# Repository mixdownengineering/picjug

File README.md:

PICJUG
======

An inexpensive USB JTAG, UART and GPIO design based on the PIC18(L)F1454.

Official website: https://www.mixdown.ca/redmine/projects/picjug

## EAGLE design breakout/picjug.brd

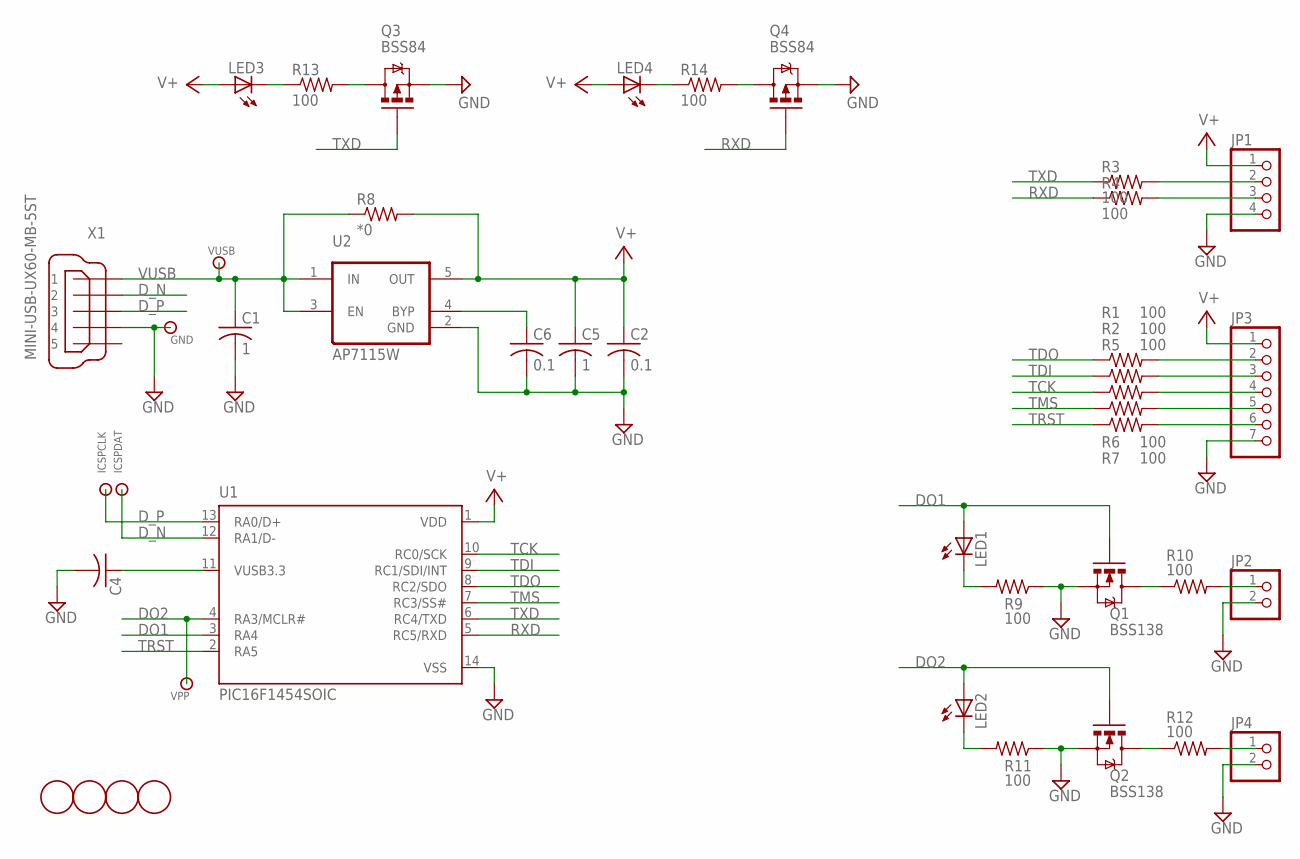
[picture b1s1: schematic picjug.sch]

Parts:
C1, C5: 1; C0805
C2, C6: 0.1; C0805
C4: C-USC0805; C0805
GND: TESTPOINTMILLMAX_0900_SMALL; 0900-SERIES-SM
ICSPCLK: TESTPOINTMILLMAX_0900_SMALL; 0900-SERIES-SM
ICSPDAT: TESTPOINTMILLMAX_0900_SMALL; 0900-SERIES-SM
JP1: PINHD-1X4; 1X04
JP2, JP4: PINHD-1X2; 1X02
JP3: PINHD-1X7; 1X07
LED1, LED2, LED3, LED4: LEDCHIP-LED0805; CHIP-LED0805
Q1, Q2: BSS138; SOT23-3
Q3, Q4: BSS84; SOT23
R1, R2, R3, R4, R5, R6, R7, R9, R10, R11, R12, R13, R14: 100; R0805
R8: *0; R0805
U1: PIC16F1454SOIC; SOIC14
U2: AP7115W; SOT25
U$1, U$2, U$3, U$4: MOUNTING_HOLENO_4; HOLE_MTG_NO4
VPP: TESTPOINTMILLMAX_0900_SMALL; 0900-SERIES-SM
VUSB: TESTPOINTMILLMAX_0900_SMALL; 0900-SERIES-SM
X1: MINI-USB-UX60-MB-5ST; UX60-MB-5ST

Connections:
DO1: LED1.A, Q1.1 (G), U1.3 (RA4)
DO2: LED2.A, Q2.1 (G), U1.4 (RA3/MCLR#), VPP.P$1
D_N: ICSPDAT.P$1, U1.12 (RA1/D-), X1.2
D_P: ICSPCLK.P$1, U1.13 (RA0/D+), X1.3
GND: C1.2, C2.2, C4.2, C5.2, C6.2, GND.P$1, JP1.4, JP2.2, JP3.7, JP4.2, Q1.2 (S), Q2.2 (S), Q3.2 (S), Q4.2 (S), R9.1, R11.1, U1.14 (VSS), U2.2 (GND), X1.4
unnamed: JP2.1, R10.2
unnamed: C6.1, U2.4 (BYP)
unnamed: JP3.2, R1.2
unnamed: C4.1, U1.11 (VUSB3.3)
unnamed: JP1.2, R3.2
unnamed: JP1.3, R4.2
unnamed: JP3.3, R2.2
unnamed: LED1.C, R9.2
unnamed: JP3.4, R5.2
unnamed: JP3.5, R6.2
unnamed: JP3.6, R7.2
unnamed: JP4.1, R12.2
unnamed: Q1.3 (D), R10.1
unnamed: LED3.C, R13.1
unnamed: Q2.3 (D), R12.1
unnamed: Q3.3 (D), R13.2
unnamed: LED2.C, R11.2
unnamed: LED4.C, R14.1
unnamed: Q4.3 (D), R14.2
RXD: Q4.1 (G), R4.1, U1.5 (RC5/RXD)
TCK: R5.1, U1.10 (RC0/SCK)
TDI: R2.1, U1.9 (RC1/SDI/INT)
TDO: R1.1, U1.8 (RC2/SDO)
TMS: R6.1, U1.7 (RC3/SS#)
TRST: R7.1, U1.2 (RA5)
TXD: Q3.1 (G), R3.1, U1.6 (RC4/TXD)
V+: C2.1, C5.1, JP1.1, JP3.1, LED3.A, LED4.A, R8.2, U1.1 (VDD), U2.5 (OUT)
VUSB: C1.1, R8.1, U2.1 (IN), U2.3 (EN), VUSB.P$1, X1.1

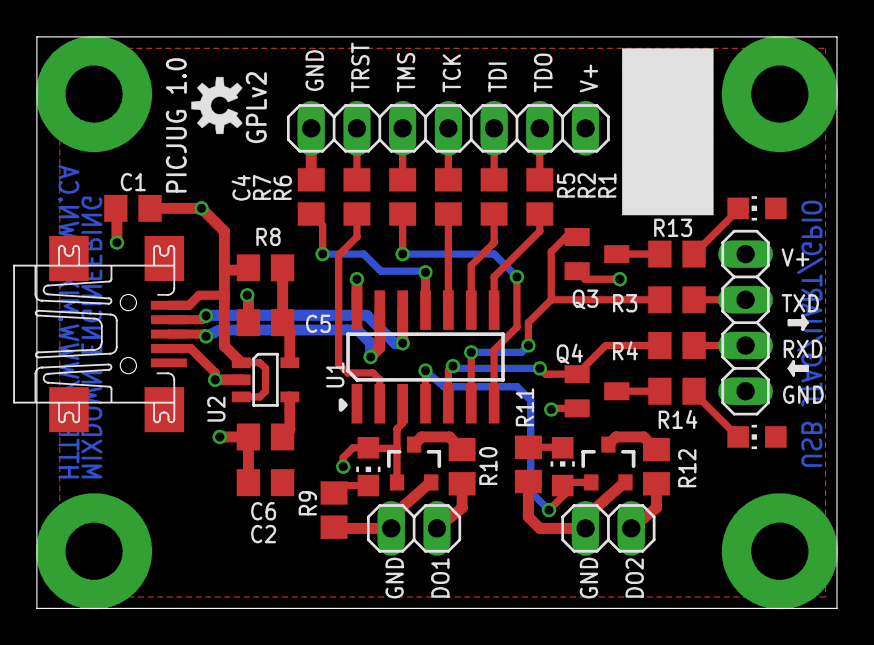
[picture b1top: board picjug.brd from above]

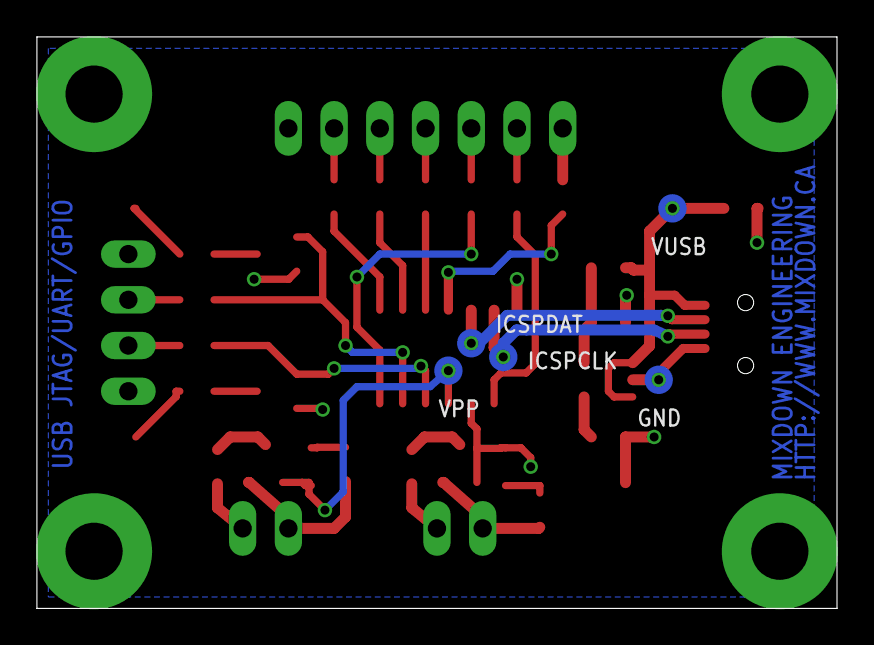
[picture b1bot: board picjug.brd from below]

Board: 2 copper layers, 44.5 x 31.8 mm, 43 parts (5 on the bottom side), 33 nets.

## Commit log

2013-09-15 moved USB connector so it is centred, added OHW logo and text
2013-09-16 add GPLv2 text to silkscreen
2013-09-16 use 0805 LEDs
2013-09-16 minor edits to board overall dimensions and text
2013-09-16 add UART arrows
2013-09-16 remove extra trace
2013-09-16 rename the design
2013-09-16 restructure the repo
2013-09-16 remove extraneous files
2013-09-16 add .gitignore
2013-09-16 add documentation
2013-09-16 add README.md
2013-09-17 add test points for in system programming
2013-09-17 fix spacing violation, re-do copper pours with 10mil lines and 24mil isolation

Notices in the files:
parts and their libraries:
SparkFun: Licensing: CC v3.0 Share-Alike You are welcome to use this library for commercial purposes.
